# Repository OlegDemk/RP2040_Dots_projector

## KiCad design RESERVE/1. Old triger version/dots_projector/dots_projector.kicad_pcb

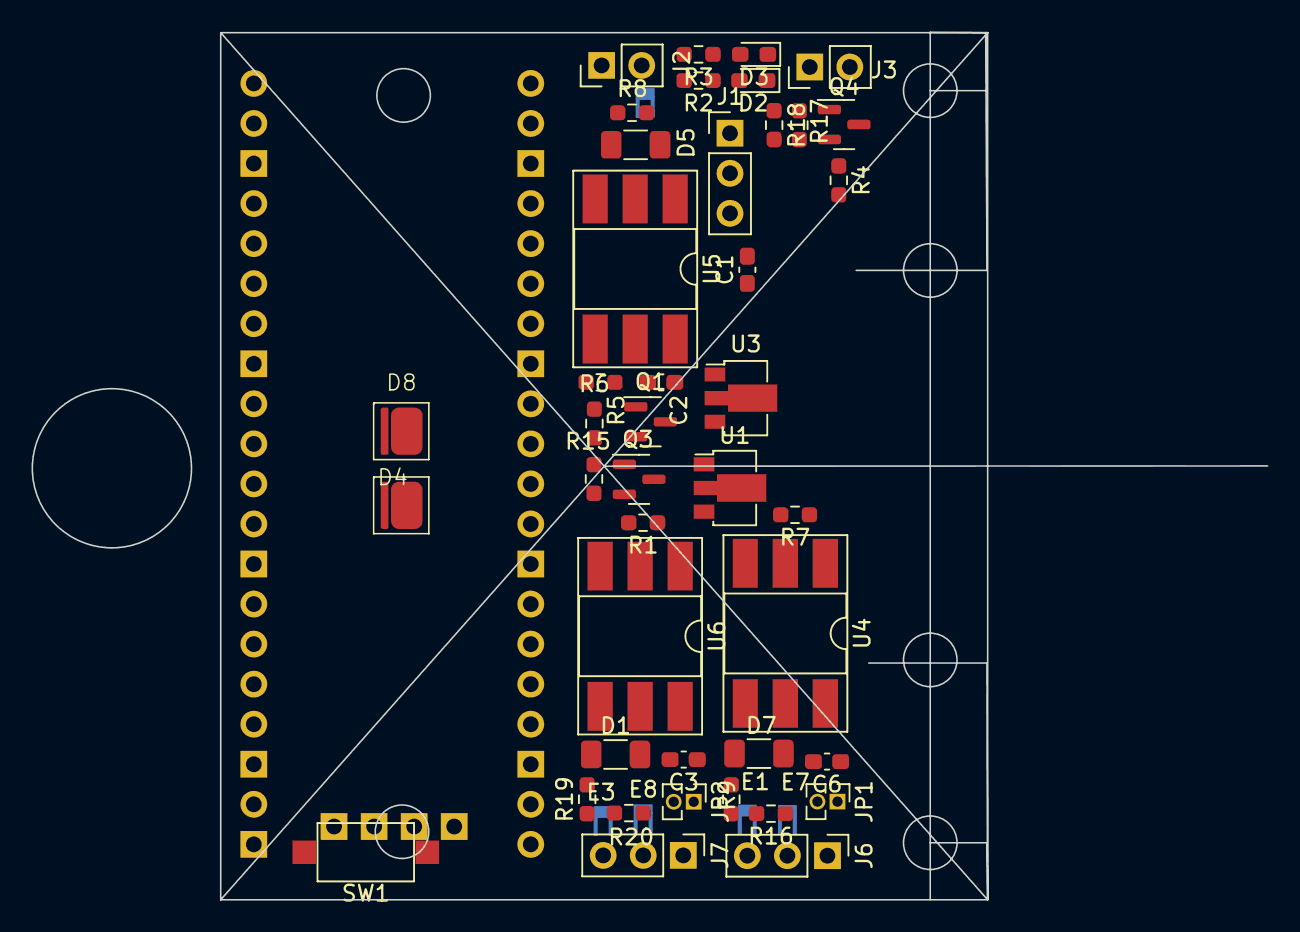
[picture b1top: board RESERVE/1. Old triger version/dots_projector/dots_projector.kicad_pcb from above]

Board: 2 copper layers, 78.3 x 55.0 mm, 48 parts (1 on the bottom side), 33 nets, no tracks yet.

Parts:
C1: 100n; C_0603_1608Metric_Pad1.08x0.95mm_HandSolder
C2, C3, C6: 0.1uF; C_0603_1608Metric_Pad1.08x0.95mm_HandSolder
D1, D5, D7: CDSOD323-T05C; R_1206_3216Metric_Pad1.30x1.75mm_HandSolder
D2, D3: LED; LED_0603_1608Metric_Pad1.05x0.95mm_HandSolder
D4, D8: BELICE-850
E1, E2, E3, E7, E8: SparkGap
J1: GND; PinHeader_1x03_P2.54mm_Vertical
J2: Projector 1; PinHeader_1x02_P2.54mm_Vertical
J3: Laser; PinHeader_1x02_P2.54mm_Vertical
J6, J7: Camera 1; PinHeader_1x03_P2.54mm_Vertical
JP1, JP2: GND_2; PinHeader_1x02_P1.27mm_Vertical
Q1, Q3, Q4: FDN358P; SOT-23
R1, R7: 220; R_0603_1608Metric_Pad0.98x0.95mm_HandSolder
R2, R3, R5: 300; R_0603_1608Metric_Pad0.98x0.95mm_HandSolder
R4: 10k; R_0603_1608Metric_Pad0.98x0.95mm_HandSolder
R6, R15, R17: 9k; R_0603_1608Metric_Pad0.98x0.95mm_HandSolder
R8: 240; R_0603_1608Metric_Pad0.98x0.95mm_HandSolder
R9, R19: 270; R_0603_1608Metric_Pad0.98x0.95mm_HandSolder
R16, R20: 100; R_0603_1608Metric_Pad0.98x0.95mm_HandSolder
R18: 10; R_0603_1608Metric_Pad0.98x0.95mm_HandSolder
SW1: SW_Push; SW_SPST_CK_RS282G05A3
U1, U3: AMC7135; SOT-89-3
U2: WeAct-RP2040-Pico
U4, U5, U6: H11L2; DIP-6_W8.89mm_SMDSocket_LongPads

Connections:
+3.3V: C2.1, Q4.2 (S), R4.1, R5.1, R17.2, U2.36 (GP24), U5.6
+5F: C3.1, C6.1, E1.2, E3.2, J6.3, J7.3, R9.1, R19.1, U4.6, U6.6
+5V: Q1.2 (S), Q3.2 (S), R6.2, R15.2, U2.40 (VBUS)
DOTS_PROJECTOR_1: Q3.1 (G), R15.1, U2.5 (GP3)
DOTS_PROJECTOR_2: Q1.1 (G), R6.1, U2.4 (GP2)
GND: C1.2, C2.2, D2.1 (K), D3.1 (K), D4.1 (K), D8.1 (K), J1.1, J1.2, J1.3, J3.2, SW1.2, U1.2 (GND), U2.18 (GND), U2.23 (GND), U2.38 (GND), U3.2 (GND), U4.2, U5.5, U6.2
GND1: C3.2, C6.2, D5.2 (A2), E2.1, J2.1, U5.2
GND2: D1.2 (A2), D7.2 (A2), E1.1, E3.1, E7.1, E8.1, JP1.2 (B), JP2.2 (B), U4.5, U6.5
LED_1: R3.2, U2.10 (GP7)
LED_2: R2.2, U2.9 (GP6)
LESER_LINE: Q4.1 (G), R17.1, U2.6 (GP4)
unnamed: D1.1 (A1), R19.2, R20.2, U6.4
unnamed: D2.2 (A), R2.1
unnamed: D3.2 (A), R3.1
unnamed: D4.2 (A), U1.1 (VO)
unnamed: D5.1 (A1), R8.2, U5.1
unnamed: D7.1 (A1), R9.2, R16.2, U4.4
unnamed: D8.2 (A), U3.1 (VO)
unnamed: E2.2, J2.2, R8.1
unnamed: J3.1, R18.1
unnamed: J6.1, JP1.1 (A)
unnamed: E7.2, J6.2, R16.1
unnamed: J7.1, JP2.1 (A)
unnamed: E8.2, J7.2, R20.1
unnamed: Q1.3 (D), U3.3 (VI)
unnamed: Q3.3 (D), U1.3 (VI)
unnamed: Q4.3 (D), R18.2
unnamed: R1.1, U6.1
unnamed: R7.1, U4.1
TRIG_INPUT: R5.2, U2.1 (GP0), U5.4
TRIG_OUTPUT_1: R7.2, U2.2 (GP1)
TRIG_OUTPUT_2: R1.2, U2.12 (GP9)
USER_BUTTON: C1.1, R4.2, SW1.1, U2.11 (GP8)

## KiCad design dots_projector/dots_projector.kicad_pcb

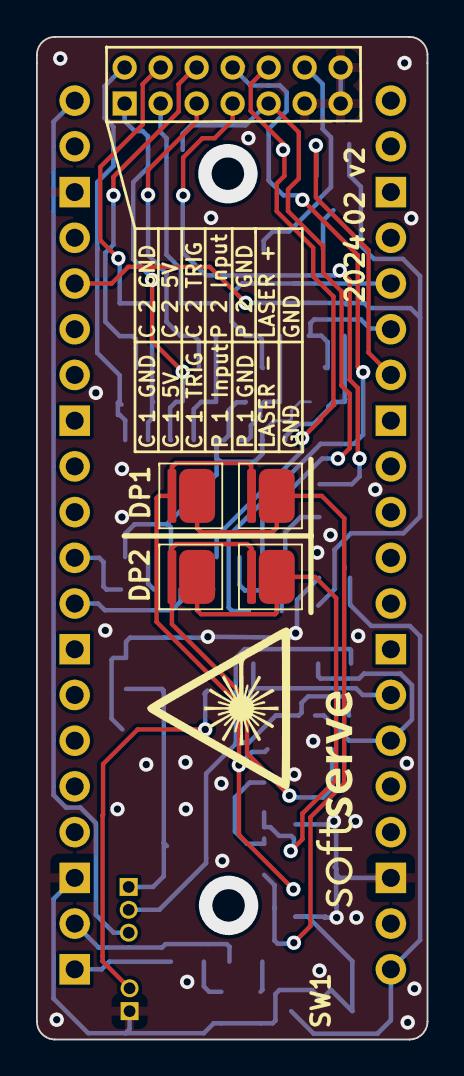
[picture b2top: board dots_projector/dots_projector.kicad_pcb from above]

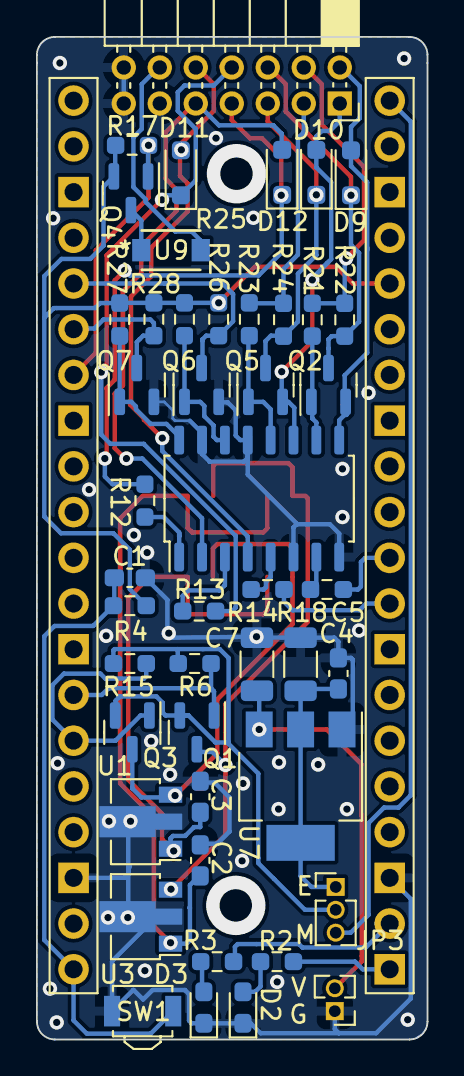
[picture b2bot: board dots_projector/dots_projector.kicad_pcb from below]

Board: 2 copper layers, 21.7 x 55.7 mm, 51 parts (47 on the bottom side), 42 nets.

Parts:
C1, C5: 100n; C_0603_1608Metric_Pad1.08x0.95mm_HandSolder
C2, C3: 1u; C_0603_1608Metric_Pad1.08x0.95mm_HandSolder
C4, C7: 22u; C_1206_3216Metric
D1, D4, D5, D8: BELICE-850
D2, D3: LED; LED_0603_1608Metric_Pad1.05x0.95mm_HandSolder
D9, D10, D11, D12: CDSOD323-T05C; D_SOD-323_HandSoldering
J2: Conn_02x07_Top_Bottom; PinSocket_2x07_P2.00mm_Horizontal
J4: External power; PinHeader_1x02_P1.27mm_Vertical
JP3: Jumper_3_Bridged12; PinHeader_1x03_P1.27mm_Vertical
Q1, Q3, Q4: FDN358P; SOT-23
Q2, Q5, Q6, Q7: S8050; SOT-23
R2, R3: 300; R_0603_1608Metric_Pad0.98x0.95mm_HandSolder
R4: 10k; R_0603_1608Metric_Pad0.98x0.95mm_HandSolder
R6, R15, R17: 9k; R_0603_1608Metric_Pad0.98x0.95mm_HandSolder
R12, R13, R14, R18: 220; R_0603_1608Metric_Pad0.98x0.95mm_HandSolder
R21, R22, R23, R24, R25, R26, R27, R28: 5.1k; R_0603_1608Metric_Pad0.98x0.95mm_HandSolder
SW1: SW_Push; SW_SPST_B3U-3000P
U1, U3: AMC7135; SOT-89-3
U2: WeAct-RP2040-Pico
U7: AMS1117-5.0; SOT-223-3_TabPin2
U9: AL5809-20P1-7; POWERDI123-C2_DIO
U10: TLP291-4; SOIC-16_4.55x10.3mm_P1.27mm

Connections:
+3.3V: Q4.2 (S), R4.1, R17.2, R25.2, R26.2, R27.2, R28.2, U2.36 (GP24)
+5P: JP3.3 (B), U2.40 (VBUS)
+5V: JP3.2 (C), Q1.2 (S), Q3.2 (S), R6.2, R15.2
CAM 1 5V: J2.3, R23.2, R24.2
CAM 1 GND: D10.2 (A2), J2.1, Q5.2 (E), U10.11
CAM 1 TRIG: D10.1 (A1), J2.5, Q5.3 (C), R24.1
CAM 2 5V: J2.4, R21.2, R22.2
CAM 2 GND: D9.2 (A2), J2.2, Q2.2 (E), U10.9
CAM 2 TRIG: D9.1 (A1), J2.6, Q2.3 (C), R22.1
DOTS_PROJECTOR_1: Q3.1 (G), R15.1, U2.15 (GP11)
DOTS_PROJECTOR_2: Q1.1 (G), R6.1, U2.14 (GP10)
GND: C1.2, C2.2, C3.2, C4.2, C5.2, C7.2, D2.1 (K), D3.1 (K), J2.11, J2.13, J2.14, J4.1, Q6.2 (E), Q7.2 (E), SW1.2, U1.2 (GND), U2.18 (GND), U2.23 (GND), U2.38 (GND), U3.2 (GND), U7.1 (GND), U10.6, U10.8, U10.13, U10.15
LED_1: R3.2, U2.22 (GP17)
LED_2: R2.2, U2.21 (GP16)
Lazer OUT: Q4.1 (G), R17.1, U2.7 (GP5)
unnamed: D1.2 (A), D8.2 (A), Q1.3 (D), U3.3 (VI)
unnamed: C2.1, D1.1 (K), D8.1 (K), U3.1 (VO)
unnamed: D2.2 (A), R2.1
unnamed: D3.2 (A), R3.1
unnamed: D4.2 (A), D5.2 (A), Q3.3 (D), U1.3 (VI)
unnamed: C3.1, D4.1 (K), D5.1 (K), U1.1 (VO)
unnamed: J2.12, U9.2 (OUT)
unnamed: C7.1, J4.2, U7.3 (VI)
unnamed: C4.1, C5.1, JP3.1 (A), U7.2 (VO)
unnamed: Q2.1 (B), R21.1, U10.10
unnamed: Q4.3 (D), U9.1 (IN)
unnamed: Q5.1 (B), R23.1, U10.12
unnamed: Q6.1 (B), R25.1, U10.14
unnamed: Q7.1 (B), R27.1, U10.16
unnamed: R12.1, U10.1
unnamed: R13.1, U10.3
unnamed: R14.1, U10.5
unnamed: R18.1, U10.7
PRJ 1 GND: D12.2 (A2), J2.9, U10.2
PRJ 1 Input: D12.1 (A1), J2.7, R12.2
PRJ 2 GND: D11.2 (A2), J2.10, U10.4
PRJ 2 Input: D11.1 (A1), J2.8, R13.2
TRIG_INPUT_PRJ_1: Q7.3 (C), R28.1, U2.6 (GP4)
TRIG_INPUT_PRJ_2: Q6.3 (C), R26.1, U2.5 (GP3)
TRIG_OUTPUT_1: R14.2, U2.29 (GP22)
TRIG_OUTPUT_2: R18.2, U2.30 (GP26)
USER_BUTTON: C1.1, R4.2, SW1.1, U2.20 (GP15)
